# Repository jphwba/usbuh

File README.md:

# Usbuh

This is a USB Hub that features USB-C input, an Auxilary Port with Audio in and out, three USB-A 2.0 ports, two USB-C 2.0 ports and a micro SD Card slot. The main USB hub controllers are two FE1.1s's, a GL823K for the micro-sd controller, an AMS1117-3.3 to step down 5v connections into 3v3 and a PCM2902E for the audio controller. I made this because on my desk the area where my PC is requires the top IO to be blocked which had all of these ports and there was no space to run a cable it was a very tight gap so my current solution is running a $5 temu adapter which goes through a USB-C to USB-A adapter ($0.30 from temu) and a USB1.0 extension cable, so my devices do run pretty slow. So I decided to make this. SInce I'm not very experienced with KiCad and with PCB's and everything, I found USB3.0 a bit more complex and I realised that my design was USB2.0 only too far into the project so I just stuck with 2.0. I also decided later in the project that I wanted an aux port since my headset has an audio/mic combo port and my PC only has split and the adapter I used doesn't work. 

## Printing Notice
Please print 5 connector brakets as there is only 1 in the step file.

## Assembly

The USB Hub has a pretty simple assembly requiring only 4 screws. First in the base plate 4 heatset inserts (M2x3.2mm) go into the standoffs. Then the pcb just goes on top and is screwed in. After this, the walls are placed just on top of the base plate and is attatched with connector brackets I made which go along the sides. Then the top plate just props ontop of the walls and then the front cover is attatched by just pressing it into the front of the assembly. 

## Images

### PCB

### PCB Render

### Schematic

### PCB Order

## Bill of Materials: PLEASE NOTE ALL PRICES ARE IN AUSTRALIAN DOLLARS
|Reference                |Qty|Value                      |Footprint                                                            |Datasheet                                                                        |Item Name                                                                                                                       |Qty|Variation                                  |Price (AUD)|Shipping Fee (If Applicable)|Reference                                                                                                                                                                                                                                                                                                                                                                                                                                                                                                                                                                                                                                                                                                                                                                      |
|Reference                |Qty|Value                      |Footprint                                                            |Datasheet                                                                        |Item Name              |Qty|Variation                                                                                      |Price (USD)|Shipping Fee (If Applicable)|Reference                                                         |
|-------------------------|---|---------------------------|---------------------------------------------------------------------|---------------------------------------------------------------------------------|-----------------------|---|-----------------------------------------------------------------------------------------------|-----------|----------------------------|------------------------------------------------------------------|
|AUX_1                    |1  |AudioJack4                 |Connector_Audio:Jack_3.5mm_PJ320D_Horizontal                         |                                                                                 |PJ-320D                |10 |3.5mm Headphone Jack 0.5A 30V Surface Mount                                                    | $0.51     |                            |https://www.lcsc.com/product-detail/C431535.html                  |
|C1,C2,C8,C9,C13          |5  |10uF                       |Capacitor_SMD:C_0805_2012Metric                                      |                                                                                 |CS2012X7R106M100NRE    |10 |10uF �20% 10V Ceramic Capacitor X7R 0805                                                       | $0.81     |                            |https://www.lcsc.com/product-detail/C5189822.html                 |
|C3,C6,C7,C10,C15         |5  |100nF                      |Capacitor_SMD:C_0805_2012Metric                                      |                                                                                 |CL21B104KBCNNNC        |20 |100nF �10% 50V Ceramic Capacitor X7R 0805                                                      | $0.30     |                            |https://www.lcsc.com/product-detail/C1711.html                    |
|C4,C5,C11,C12,C22,C23    |6  |22pF                       |Capacitor_SMD:C_0805_2012Metric                                      |                                                                                 |CL21C220JBANNNC        |50 |22pF �5% 50V Ceramic Capacitor C0G 0805                                                        | $0.62     |                            |https://www.lcsc.com/product-detail/C1804.html                    |
|C14                      |1  |22uF                       |Capacitor_SMD:C_1206_3216Metric                                      |                                                                                 |CL21A226MOQNNNE        |10 |22uF �20% 16V Ceramic Capacitor X5R 0805                                                       | $1.06     |                            |https://www.lcsc.com/product-detail/C98190.html                   |
|C16,C17,C19,C20,C21,C26  |6  |1uF                        |Capacitor_SMD:C_0805_2012Metric                                      |                                                                                 |CL21B105KAFNNNE        |10 |1uF �10% 25V Ceramic Capacitor X7R 0805                                                        | $0.41     |                            |https://www.lcsc.com/product-detail/C116352.html                  |
|C18                      |1  |2.2uF                      |Capacitor_SMD:C_0805_2012Metric                                      |                                                                                 |CL21A225KBQNNNE        |10 |2.2uF �10% 50V Ceramic Capacitor X5R 0805                                                      | $0.54     |                            |https://www.lcsc.com/product-detail/C377773.html                  |
|C24,C25                  |2  |100uF                      |Capacitor_SMD:C_1210_3225Metric                                      |                                                                                 |CL21A107MQYNNWE        |4  |100uF �20% 6.3V Ceramic Capacitor X5R 0805                                                     | $2.95     |                            |https://www.lcsc.com/product-detail/C6882730.html                 |
|F1,F2,F5,F6,F7           |5  |1A                         |Fuse:Fuse_1206_3216Metric                                            |                                                                                 |BSMD1206-100-30V       |10 |Polymeric PTC Resettable Fuse 30V 1A Surface Mount 1206                                        | $1.01     |                            |https://www.lcsc.com/product-detail/C5358568.html                 |
|Input1,USB_C_1,USB_C_2   |3  |USB_C_Receptacle_USB2.0_16P|Connector_USB:USB_C_Receptacle_GCT_USB4105-xx-A_16P_TopMnt_Horizontal|https://www.usb.org/sites/default/files/documents/usb_type-c.zip                 |USB4105-GF-A-060       |3  |USB 2.0 1 12P -40?~+85? Surface Mount, Right Angle SMD USB, DVI, HDMI Connector Assemblies RoHS| $4.42     |                            |https://www.lcsc.com/product-detail/C3025063.html                 |
|MICRO_SD1                |1  |Micro_SD_Card              |Connector_Card:microSD_HC_Hirose_DM3AT-SF-PEJM5                      |https://www.we-online.com/components/products/datasheet/693072010801.pdf         |DM3AT-SF-PEJM5         |1  |Micro SD card (TF card) Connector and Ejector Push-Push Surface Mount                          | $1.40     |                            |https://www.lcsc.com/product-detail/C114218.html                  |
|R1,R2                    |2  |5.1k                       |Resistor_SMD:R_0805_2012Metric                                       |                                                                                 |0805W8F5101T5E         |100|5.1k? �1% 125mW 0805 Thick Film Resistor                                                       | $0.53     |                            |https://www.lcsc.com/product-detail/C27834.html                   |
|R3,R11                   |2  |2.7k                       |Resistor_SMD:R_0805_2012Metric                                       |                                                                                 |FRC0805J272 TS         |100|2.7k? �5% 125mW 0805 Thick Film Resistor                                                       | $0.32     |                            |https://www.lcsc.com/product-detail/C2907305.html                 |
|R4,R5,R6,R7,R8,R9,R10,R12|8  |10k                        |Resistor_SMD:R_0805_2012Metric                                       |                                                                                 |FRC0805F1002TS         |100|10k? �1% 125mW 0805 Thick Film Resistor                                                        | $0.34     |                            |https://www.lcsc.com/product-detail/C2907219.html                 |
|R13,R14,R15,R16          |4  |56k                        |Resistor_SMD:R_0805_2012Metric                                       |                                                                                 |0805W8F5602T5E         |100|56k? �1% 125mW 0805 Thick Film Resistor                                                        | $0.30     |                            |https://www.lcsc.com/product-detail/C17756.html                   |
|R17,R18                  |2  |22                         |Resistor_SMD:R_0805_2012Metric                                       |                                                                                 |FRC0805J220 TS         |100|22? �5% 125mW 0805 Thick Film Resistor                                                         | $0.33     |                            |https://www.lcsc.com/product-detail/C2907310.html                 |
|R19                      |1  |2.2k                       |Resistor_SMD:R_0805_2012Metric                                       |                                                                                 |0805W8F2201T5E         |100|2.2k? �1% 125mW 0805 Thick Film Resistor                                                       | $0.44     |                            |https://www.lcsc.com/product-detail/C17520.html                   |
|U1,U2                    |2  |FE1.1s                     |Package_SO:SSOP-28_3.9x9.9mm_P0.635mm                                |https://cdn-shop.adafruit.com/product-files/2991/FE1.1s+Data+Sheet+(Rev.+1.0).pdf|FE1.1S-BSOP28BCN       |2  |4 USB Hub 480Mbps USB 2.0 SSOP-28-150mil Interface Controllers RoHS                            | $1.39     |                            |https://www.lcsc.com/product-detail/C9359.html                    |
|U3                       |1  |GL823K                     |GL823K:SOP64P600X175-16N                                             |                                                                                 |GL823K-HCY04           |1  |USB to SD 480Mbps USB 2.0 SSOP-16-150mil Interface Controllers RoHS                            | $0.46     |                            |https://www.lcsc.com/product-detail/C284879.html                  |
|U4                       |1  |AMS1117-3.3                |Package_TO_SOT_SMD:SOT-223-3_TabPin2                                 |http://www.advanced-monolithic.com/pdf/ds1117.pdf                                |AMS1117-3.3            |5  |3.3V Positive Fixed SOT-223 Voltage Regulators - Linear, Low Drop Out (LDO) Regulators RoHS    | $1.05     |                            |https://www.lcsc.com/product-detail/C6186.html                    |
|U5                       |1  |PCM2902                    |Package_SO:SSOP-28_5.3x10.2mm_P0.65mm                                |http://www.ti.com/lit/ds/symlink/pcm2902c.pdf                                    |PCM2902CDBR            |1  |Encoder/decoder USB 8kHz~48kHz SSOP-28 CODECS RoHS                                             | $12.21    |                            |https://www.lcsc.com/product-detail/C2651869.html                 |
|USB_A_1                  |1  |USB_A                      |Connector_USB:USB_A_Receptacle_GCT_USB1046                           |                                                                                 |USB1046-GF-0190-L-B-A  |1  |USB 2.0 1 4P -40?~+85? SMD USB, DVI, HDMI Connector Assemblies RoHS                            | $1.35     |                            |https://www.lcsc.com/product-detail/C6307429.html                 |
|USB_A_STACKED_2&3        |1  |USB_A_Stacked              |Connector_USB:USB_A_Wuerth_61400826021_Horizontal_Stacked            |                                                                                 |907-111A1012D10200     |5  |USB-A (USB TYPE-A) Receptacle Connector 8 Position Through Hole                                | $0.93     |                            |https://www.lcsc.com/product-detail/C2341.html                    |
|Y1,Y2,Y3                 |3  |12MHz                      |Crystal:Crystal_SMD_3225-4Pin_3.2x2.5mm                              |                                                                                 |X322512MSB4SI          |5  |Crystal 12MHz �10ppm 20pF SMD3225-4P                                                           | $0.48     |                            |https://www.lcsc.com/product-detail/C9002.html                    |
|Heatset Inserts          |4  |M2x3.2mm                   |                                                                     |                                                                                 |M2x3.2mm heatset insert|4  |Brass Threaded Heat-Set Insert [M2x3x3.2]                                                      | $2.16     | $10.00                     |https://www.3dprintergear.com.au/m2-brass-threaded-heat-set-insert|
|PCB                      |1  |90x55                      |                                                                     |                                                                                 |JLPCB                  |   |                                                                                               | $23.00    |                            |                                                                  |
|Printing Legion          |1  |                           |                                                                     |                                                                                 |                       |   |                                                                                               | $14.00    |                            |                                                                  |
|LCSC Shipping            |   |                           |                                                                     |                                                                                 |LCSC Shipping - 4PX    |   |                                                                                               | $14.97    |                            |                                                                  |
|                         |   |                           |Total Price:                                                         |                                                                                 |                       |   |                                                                                               | $98.29    |                            |                                                                  |
|                         |   |                           |                                                                     |                                                                                 |                       |   |                                                                                               |           |                            |                                                                  |
|                         |   |                           |                                                                     |                                                                                 |                       |   |                                                                                               |           |                            |                                                                  |
|                         |   |                           |                                                                     |                                                                                 |                       |   |                                                                                               |           |                            |                                                                  |

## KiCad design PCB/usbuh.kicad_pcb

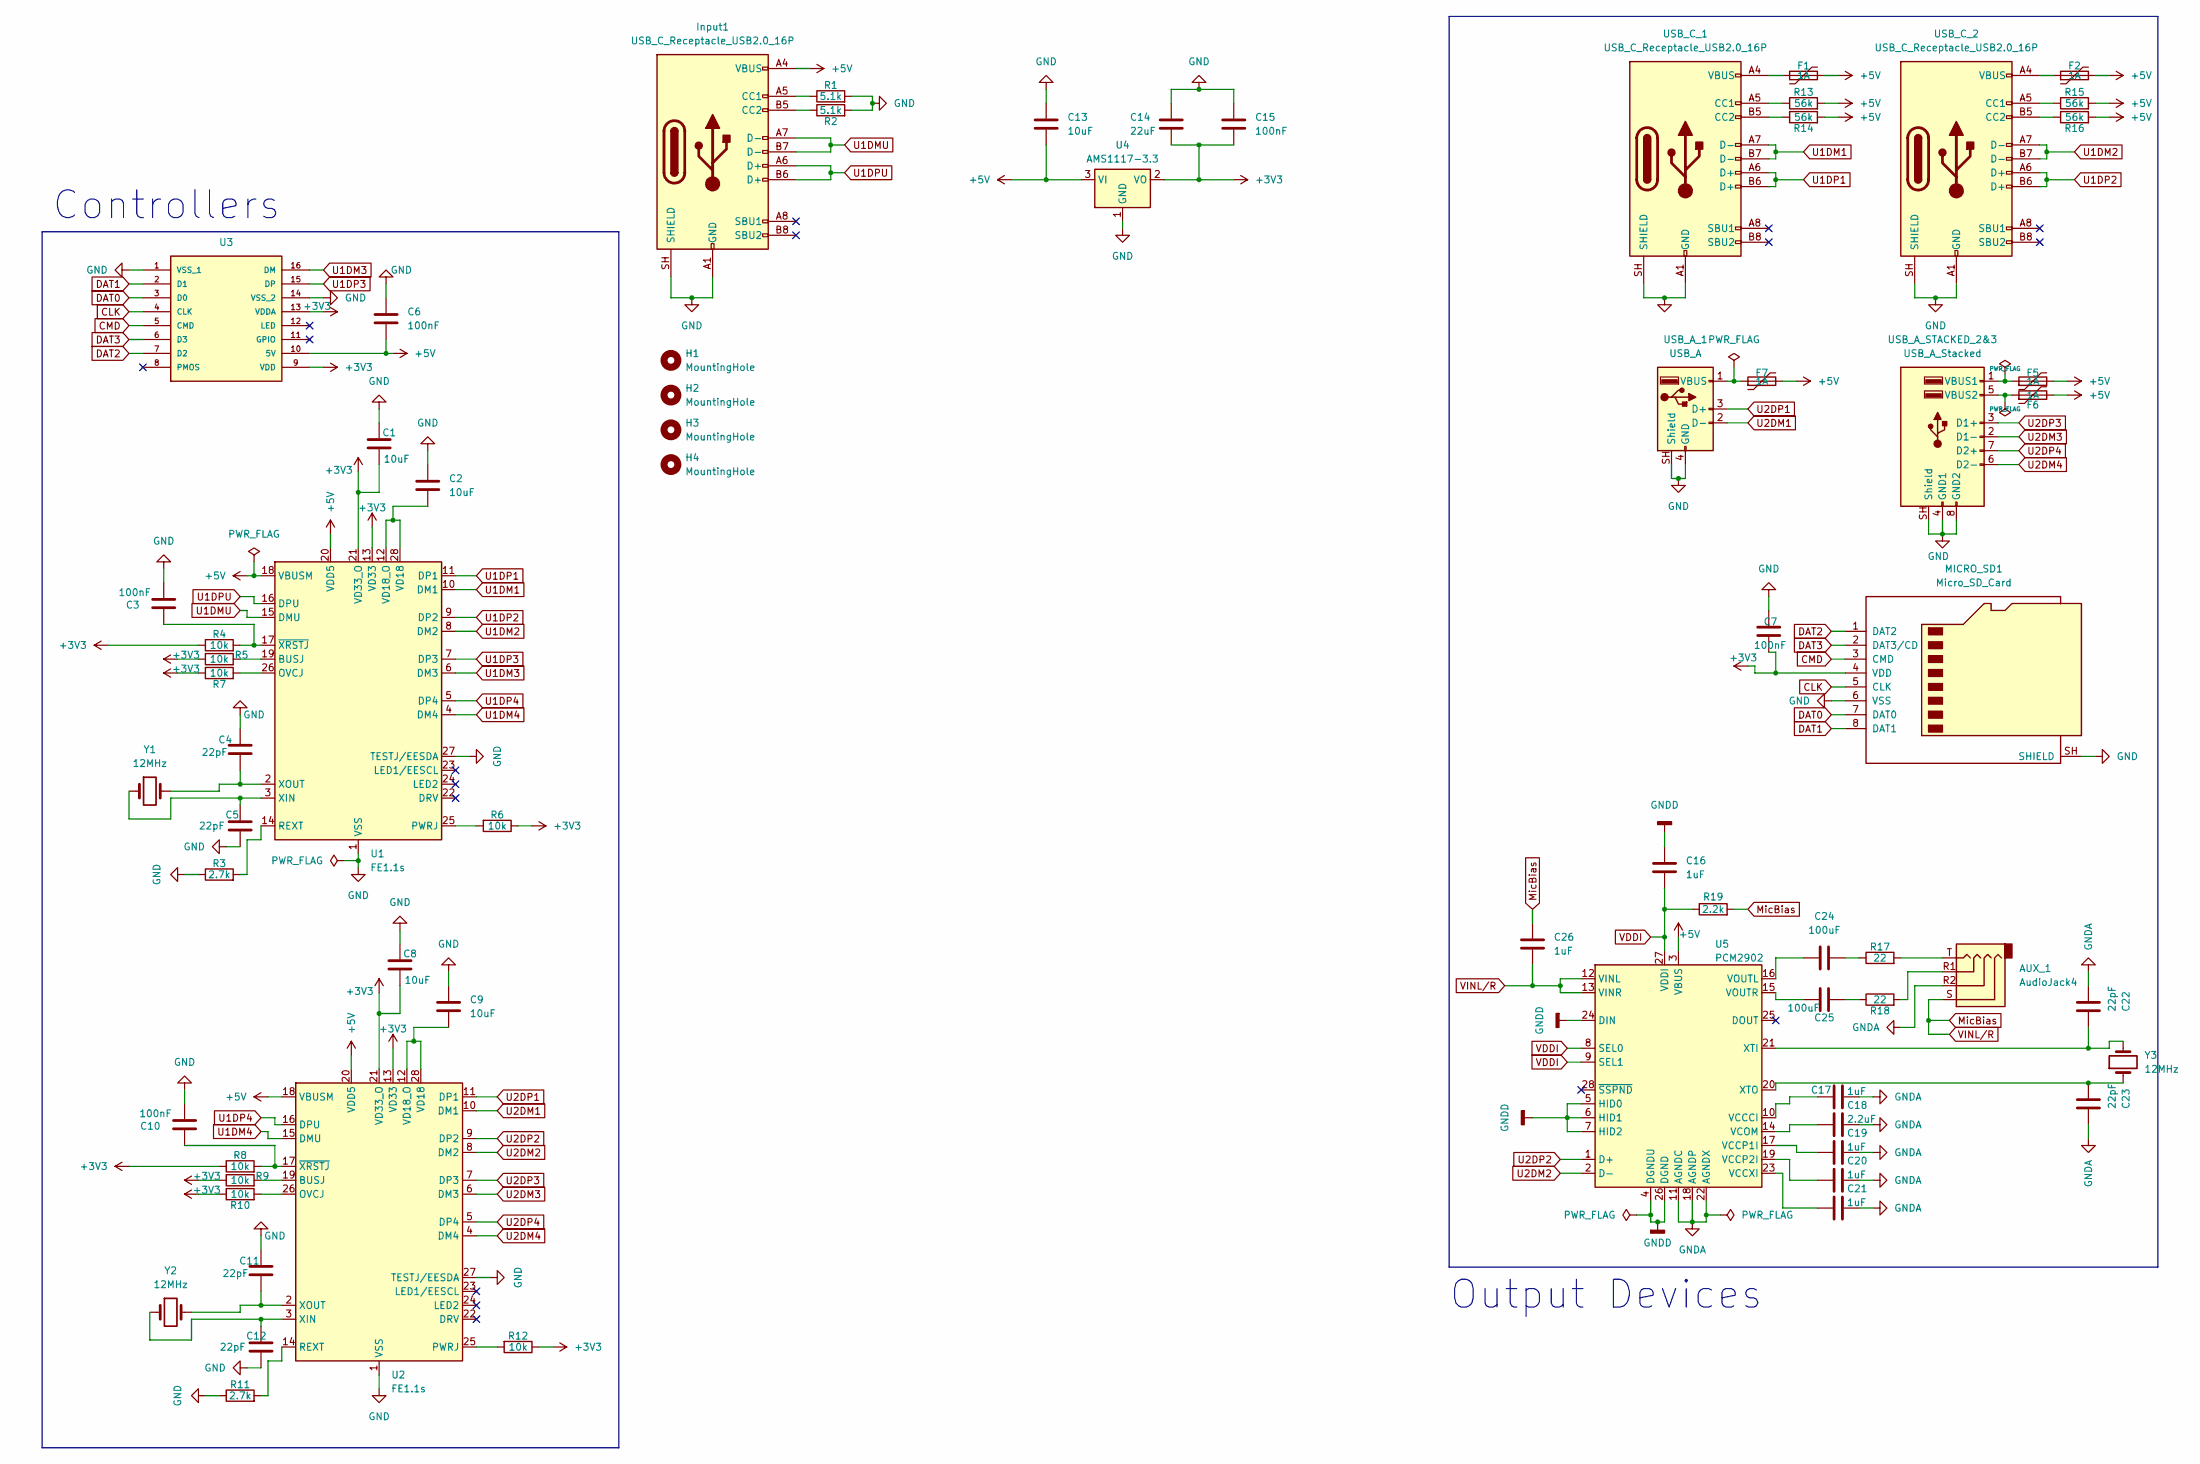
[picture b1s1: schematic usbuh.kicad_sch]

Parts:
AUX_1: AudioJack4; Jack_3.5mm_PJ320D_Horizontal
C1, C2, C8, C9, C13: 10uF; C_0805_2012Metric
C3, C6, C7, C10, C15: 100nF; C_0805_2012Metric
C4, C5, C11, C12, C22, C23: 22pF; C_0805_2012Metric
C14: 22uF; C_1206_3216Metric
C16, C17, C19, C20, C21, C26: 1uF; C_0805_2012Metric
C18: 2.2uF; C_0805_2012Metric
C24, C25: 100uF; C_1210_3225Metric
F1, F2, F5, F6, F7: 1A; Fuse_1206_3216Metric
H1, H2, H3, H4: MountingHole; MountingHole_2.1mm
Input1: USB_C_Receptacle_USB2.0_16P; USB_C_Receptacle_GCT_USB4105-xx-A_16P_TopMnt_Horizontal
MICRO_SD1: Micro_SD_Card; microSD_HC_Hirose_DM3AT-SF-PEJM5
R1, R2: 5.1k; R_0805_2012Metric
R3, R11: 2.7k; R_0805_2012Metric
R4, R5, R6, R7, R8, R9, R10, R12: 10k; R_0805_2012Metric
R13, R14, R15, R16: 56k; R_0805_2012Metric
R17, R18: 22; R_0805_2012Metric
R19: 2.2k; R_0805_2012Metric
U1, U2: FE1.1s; SSOP-28_3.9x9.9mm_P0.635mm
U3: SOP64P600X175-16N; MANUFACTURER_PART_NUMBER GL823K
U4: AMS1117-3.3; SOT-223-3_TabPin2
U5: PCM2902; SSOP-28_5.3x10.2mm_P0.65mm
USB_A_1: USB_A; USB_A_Receptacle_GCT_USB1046
USB_A_STACKED_2&3: USB_A_Stacked; USB_A_Wuerth_61400826021_Horizontal_Stacked
USB_C_1, USB_C_2: USB_C_Receptacle_USB2.0_16P; USB_C_Receptacle_GCT_USB4105-xx-A_16P_TopMnt_Horizontal
Y1, Y2, Y3: 12MHz; Crystal_SMD_3225-4Pin_3.2x2.5mm

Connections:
+3V3: C1.1, C7.2, C8.1, C14.2, C15.2, MICRO_SD1.4 (VDD), R4.1, R5.1, R6.1, R7.1, R8.1, R9.1, R10.1, R12.1, U1.13 (VD33), U1.21 (VD33_O), U2.13 (VD33), U2.21 (VD33_O), U3.9 (VDD), U3.13 (VDDA), U4.2 (VO)
+5V: C6.2, C13.2, F1.2, F2.2, F5.2, F6.2, F7.2, Input1.A4 (VBUS), Input1.A9 (VBUS), Input1.B4 (VBUS), Input1.B9 (VBUS), R13.2, R14.2, R15.2, R16.2, U1.18 (VBUSM), U1.20 (VDD5), U2.18 (VBUSM), U2.20 (VDD5), U3.10 (5V), U4.3 (VI), U5.3 (VBUS)
CLK: MICRO_SD1.5 (CLK), U3.4 (CLK)
CMD: MICRO_SD1.3 (CMD), U3.5 (CMD)
DAT0: MICRO_SD1.7 (DAT0), U3.3 (D0)
DAT1: MICRO_SD1.8 (DAT1), U3.2 (D1)
DAT2: MICRO_SD1.1 (DAT2), U3.7 (D2)
DAT3: MICRO_SD1.2 (DAT3/CD), U3.6 (D3)
GND: C1.2, C2.2, C3.2, C4.1, C5.2, C6.1, C7.1, C8.2, C9.2, C10.2, C11.1, C12.2, C13.1, C14.1, C15.1, Input1.A1 (GND), Input1.A12 (GND), Input1.B1 (GND), Input1.B12 (GND), Input1.SH (SHIELD), MICRO_SD1.6 (VSS), MICRO_SD1.SH (SHIELD), R1.2, R2.2, R3.1, R11.1, U1.1 (VSS), U1.27 (TESTJ/EESDA), U2.1 (VSS), U2.27 (TESTJ/EESDA), U3.1 (VSS_1), U3.14 (VSS_2), U4.1 (GND), USB_A_1.4 (GND), USB_A_1.SH (Shield), USB_A_STACKED_2&3.4 (GND1), USB_A_STACKED_2&3.8 (GND2), USB_A_STACKED_2&3.SH (Shield), USB_C_1.A1 (GND), USB_C_1.A12 (GND), USB_C_1.B1 (GND), USB_C_1.B12 (GND), USB_C_1.SH (SHIELD), USB_C_2.A1 (GND), USB_C_2.A12 (GND), USB_C_2.B1 (GND), USB_C_2.B12 (GND), USB_C_2.SH (SHIELD)
GNDA: AUX_1.R2, C17.2, C18.2, C19.2, C20.2, C21.2, C22.2, C23.1, U5.11 (AGNDC), U5.18 (AGNDP), U5.22 (AGNDX)
GNDD: C16.2, U5.4 (DGNDU), U5.5 (HID0), U5.6 (HID1), U5.7 (HID2), U5.24 (DIN), U5.26 (DGND)
MicBias: AUX_1.S, C26.1, C26.2, R19.2, U5.12 (VINL), U5.13 (VINR)
unnamed: AUX_1.R1, R18.2
unnamed: AUX_1.T, R17.2
unnamed: C24.2, R17.1
unnamed: C25.2, R18.1
unnamed: F1.1, USB_C_1.A4 (VBUS), USB_C_1.A9 (VBUS), USB_C_1.B4 (VBUS), USB_C_1.B9 (VBUS)
unnamed: F2.1, USB_C_2.A4 (VBUS), USB_C_2.A9 (VBUS), USB_C_2.B4 (VBUS), USB_C_2.B9 (VBUS)
unnamed: Input1.A5 (CC1), R1.1
unnamed: Input1.B5 (CC2), R2.1
unnamed: R5.2, U1.19 (BUSJ)
unnamed: R7.2, U1.26 (OVCJ)
unnamed: R6.2, U1.25 (PWRJ)
unnamed: R3.2, U1.14 (REXT)
unnamed: C2.1, U1.12 (VD18_O), U1.28 (VD18)
unnamed: C5.1, U1.3 (XIN), Y1.1
unnamed: C4.2, U1.2 (XOUT), Y1.2
unnamed: C3.1, R4.2, U1.17 (~XRSTJ)
unnamed: R9.2, U2.19 (BUSJ)
unnamed: R10.2, U2.26 (OVCJ)
unnamed: R12.2, U2.25 (PWRJ)
unnamed: R11.2, U2.14 (REXT)
unnamed: C9.1, U2.12 (VD18_O), U2.28 (VD18)
unnamed: C12.1, U2.3 (XIN), Y2.1
unnamed: C11.2, U2.2 (XOUT), Y2.2
unnamed: C10.1, R8.2, U2.17 (~XRSTJ)
unnamed: C17.1, U5.10 (VCCCI)
unnamed: C19.1, U5.17 (VCCP1I)
unnamed: C20.1, U5.19 (VCCP2I)
unnamed: C21.1, U5.23 (VCCXI)
unnamed: C18.1, U5.14 (VCOM)
unnamed: C24.1, U5.16 (VOUTL)
unnamed: C25.1, U5.15 (VOUTR)
unnamed: C22.1, U5.21 (XTI), Y3.2
unnamed: C23.2, U5.20 (XTO), Y3.1
unnamed: F7.1, USB_A_1.1 (VBUS)
unnamed: F5.1, USB_A_STACKED_2&3.1 (VBUS1)
unnamed: F6.1, USB_A_STACKED_2&3.5 (VBUS2)
unnamed: R13.1, USB_C_1.A5 (CC1)
unnamed: R14.1, USB_C_1.B5 (CC2)
unnamed: R15.1, USB_C_2.A5 (CC1)
unnamed: R16.1, USB_C_2.B5 (CC2)
U1DM1: U1.10 (DM1), USB_C_1.A7 (D-), USB_C_1.B7 (D-)
U1DM2: U1.8 (DM2), USB_C_2.A7 (D-), USB_C_2.B7 (D-)
U1DM3: U1.6 (DM3), U3.16 (DM)
U1DM4: U1.4 (DM4), U2.15 (DMU)
U1DMU: Input1.A7 (D-), Input1.B7 (D-), U1.15 (DMU)
U1DP1: U1.11 (DP1), USB_C_1.A6 (D+), USB_C_1.B6 (D+)
U1DP2: U1.9 (DP2), USB_C_2.A6 (D+), USB_C_2.B6 (D+)
U1DP3: U1.7 (DP3), U3.15 (DP)
U1DP4: U1.5 (DP4), U2.16 (DPU)
U1DPU: Input1.A6 (D+), Input1.B6 (D+), U1.16 (DPU)
U2DM1: U2.10 (DM1), USB_A_1.2 (D-)
U2DM2: U2.8 (DM2), U5.2 (D-)
U2DM3: U2.6 (DM3), USB_A_STACKED_2&3.2 (D1-)
U2DM4: U2.4 (DM4), USB_A_STACKED_2&3.6 (D2-)
U2DP1: U2.11 (DP1), USB_A_1.3 (D+)
U2DP2: U2.9 (DP2), U5.1 (D+)
U2DP3: U2.7 (DP3), USB_A_STACKED_2&3.3 (D1+)
U2DP4: U2.5 (DP4), USB_A_STACKED_2&3.7 (D2+)
VDDI: C16.1, R19.1, U5.8 (SEL0), U5.9 (SEL1), U5.27 (VDDI)

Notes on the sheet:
Output Devices
Controllers

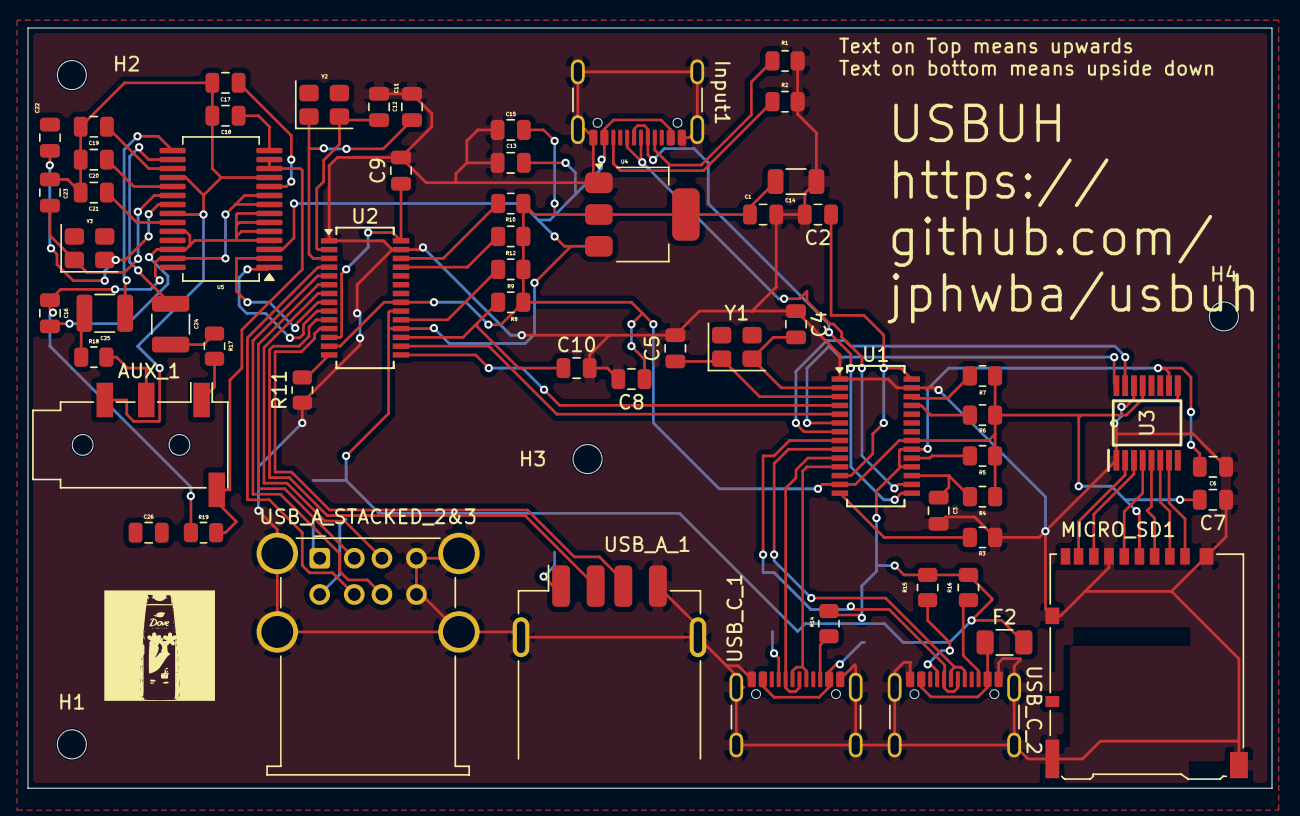
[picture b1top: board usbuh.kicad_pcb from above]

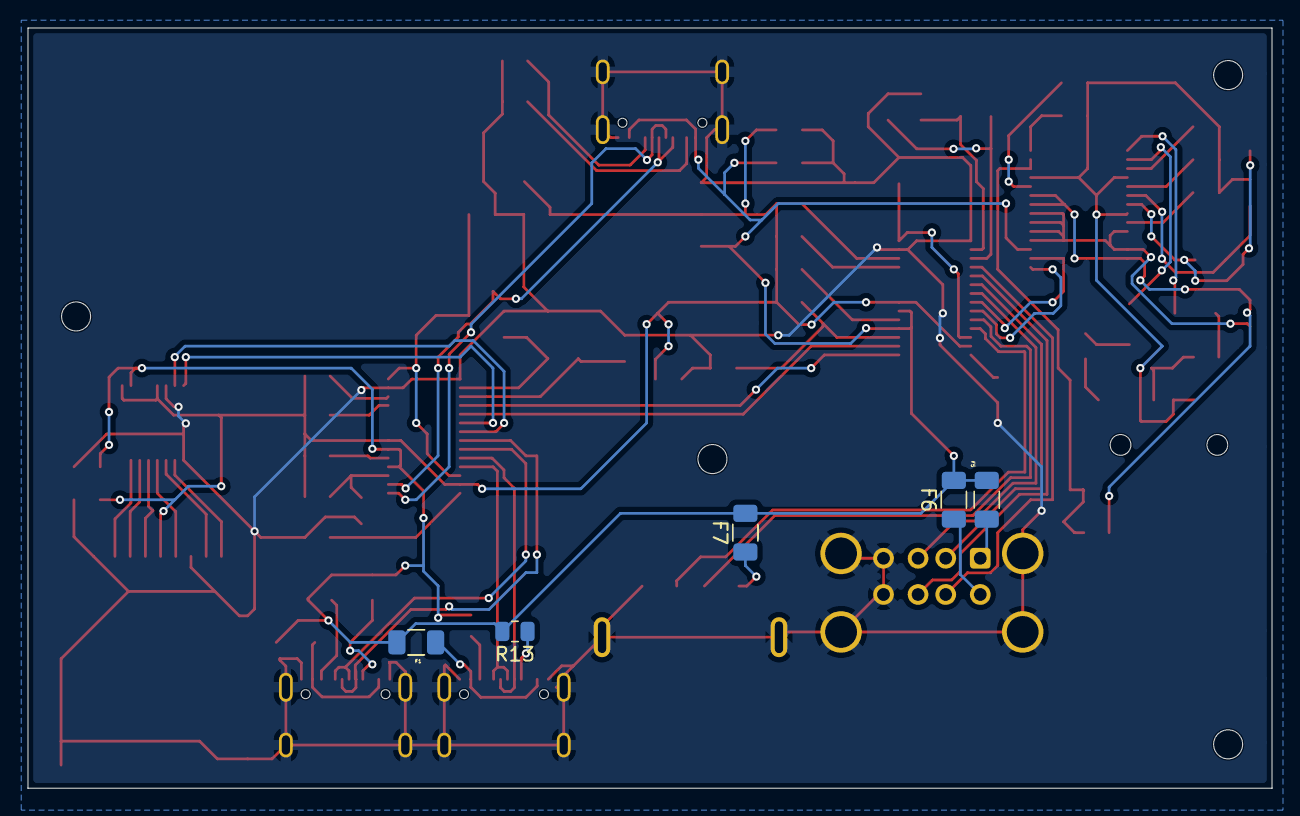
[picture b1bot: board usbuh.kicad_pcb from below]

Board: 2 copper layers, 90.0 x 55.0 mm, 69 parts (5 on the bottom side), 71 nets.

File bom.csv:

Reference,Qty,Value,Footprint,Datasheet,Item Name,Qty,Variation, Price (AUD) , Shipping Fee (If Applicable) ,Reference
AUX_1,1,AudioJack4,Connector_Audio:Jack_3.5mm_PJ320D_Horizontal,,10PCS 3.5MM Headphone Jack PJ-320D Audio Jack 4 Pin SMD SMT MP3 Accessories PJ320D,1,,$1.69,,https://www.aliexpress.com/item/4000661908135.html?spm=a2g0o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
"C1,C2,C8,C9,C13",5,10uF,Capacitor_SMD:C_0805_2012Metric,,20PCS 0805 2012 SMD Capacitor 1UF 2.2UF 4.7UF 10UF 22UF 47UF 100UF 6V3 10V 16V 25V 35V 50V 63V 100V X7R X5R K=±10% M=±20%,1,Capacitance: 0805 10UF 10V X7R K,$1.43,,https://www.aliexpress.com/item/1005007533370902.html?spm=a2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
"C3,C6,C7,C10,C15",5,100nF,Capacitor_SMD:C_0805_2012Metric,,50PCS 0805 100NF 104K 50V 100V 250V 10% X7R 2012 SMD Chip Multilayer Ceramic Capacitor ,1,(Capacitance: 0805 100NF 104K 50V),$1.76,,https://www.aliexpress.com/item/1005007533532838.html?spm=a2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
"C4,C5,C11,C12,C22,C23",6,22pF,Capacitor_SMD:C_0805_2012Metric,,100PCS 0805 C0805 20pF 50V 2012 Capacitor 1PF-47UF ( 10PF 22PF 47PF 100PF 1NF 2.2NF 10NF 100NF 1UF 2.2UF 4.7UF 10UF 22UF ) ,1,(Capacitance: 22PF),$2.15,,https://www.aliexpress.com/item/1106549969.html?spm=a2g0o.pr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
C14,1,22uF,Capacitor_SMD:C_1206_3216Metric,,20PCS 0805 2012 SMD Capacitor 1UF 2.2UF 4.7UF 10UF 22UF 47UF 100UF 6V3 10V 16V 25V 35V 50V 63V 100V X7R X5R K=±10% M=±20% ,1,(Capacitance: 0805 22UF 10V X7R K),$1.50,,https://www.aliexpress.com/item/1005007533370902.html?spm=a2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
"C16,C17,C19,C20,C21,C26",6,1uF,Capacitor_SMD:C_0805_2012Metric,,100PCS 0805 C0805 20pF 50V 2012 Capacitor 1PF-47UF ( 10PF 22PF 47PF 100PF 1NF 2.2NF 10NF 100NF 1UF 2.2UF 4.7UF 10UF 22UF ) ,1,(Capacitance: 1UF),$2.15,,https://www.aliexpress.com/item/1106549969.html?spm=a2g0o.pr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
C18,1,2.2uF,Capacitor_SMD:C_0805_2012Metric,,100PCS 0805 C0805 20pF 50V 2012 Capacitor 1PF-47UF ( 10PF 22PF 47PF 100PF 1NF 2.2NF 10NF 100NF 1UF 2.2UF 4.7UF 10UF 22UF ) ,1,(Capacitance: 2.2UF),$2.15,,https://www.aliexpress.com/item/1106549969.html?spm=a2g0o.pr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
"C24,C25",2,100uF,Capacitor_SMD:C_1210_3225Metric,,20PCS 0805 SMD Capacitor 1UF 2.2UF 4.7UF 10UF 22UF 47UF 100UF 6V3 10V 16V 25V 35V 50V 63V 100V X7R X5R K=±10% M=±20%,1,Resistance: 0805 100UF 10V X5R M,$13.29,,https://www.aliexpress.com/item/1005006815492689.html?spm=a2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
"F1,F2,F5,F6,F7",5,1A,Fuse:Fuse_1206_3216Metric,,3216 1206 0.05A 0.1A 0.12A 0.16A 0.2A 0.25A 0.5A 0.75A 1.1A 2A SMD Resettable Fuse PPTC PolySwitch Self-Recovery Fuse,1,"(AMP: 1A, Size: 1206, Temperature: 20 Pcs)",$3.38,,https://www.aliexpress.com/item/1005004273302126.html?spm=a2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
"Input1,USB_C_1,USB_C_2",3,USB_C_Receptacle_USB2.0_16P,Connector_USB:USB_C_Receptacle_GCT_USB4105-xx-A_16P_TopMnt_Horizontal,https://www.usb.org/sites/default/files/documents/usb_type-c.zip,10-100Pcs USB4105-GF-A 16Pin Type-C Female Socket SMT Top Mount PCB Receptacle USB2.0 16P Right Angle SMD Connector Replacement ,1,(Color: 10pcs),$4.89,,https://www.aliexpress.com/item/1005012606240318.html?spm=a2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
MICRO_SD1,1,Micro_SD_Card,Connector_Card:microSD_HC_Hirose_DM3AT-SF-PEJM5,https://www.we-online.com/components/products/datasheet/6930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,100% brand new original connector DM3AT-SF-PEJM5 micro SD memory card slot TF card slot 10P ,1,(Model Number: 1pcs),$0.77,$9.48,https://www.aliexpress.com/item/1005009087733553.html?spm=a2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
"R1,R2",2,5.1k,Resistor_SMD:R_0805_2012Metric,,100PCS 0805 5% 0R-10M 1R 2.2R 10R 22R 47R 100R 560R 1K2 6.8K 10K 12K 20K 47K 100K 510K 910K 1M 4.7M 9.1M 1/8W ,1,(Resistance: 5.1k),$0.55,$2.85,https://www.aliexpress.com/item/1005004542018347.html?spm=a2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
"R3,R11",2,2.7k,Resistor_SMD:R_0805_2012Metric,,100PCS 0805 5% 0R-10M 1R 2.2R 10R 22R 47R 100R 560R 1K2 6.8K 10K 12K 20K 47K 100K 510K 910K 1M 4.7M 9.1M 1/8W ,1,(Resistance: 2.7k),$0.55,$2.85,https://www.aliexpress.com/item/1005004542018347.html?spm=a2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
"R4,R5,R6,R7,R8,R9,R10,R12",8,10k,Resistor_SMD:R_0805_2012Metric,,100PCS 0805 5% 0R-10M 1R 2.2R 10R 22R 47R 100R 560R 1K2 6.8K 10K 12K 20K 47K 100K 510K 910K 1M 4.7M 9.1M 1/8W ,1,(Resistance: 10k),$0.55,$2.85,https://www.aliexpress.com/item/1005004542018347.html?spm=a2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
"R13,R14,R15,R16",4,56k,Resistor_SMD:R_0805_2012Metric,,100PCS 0805 5% 0R-10M 1R 2.2R 10R 22R 47R 100R 560R 1K2 6.8K 10K 12K 20K 47K 100K 510K 910K 1M 4.7M 9.1M 1/8W ,1,(Resistance: 56k),$0.55,$2.85,https://www.aliexpress.com/item/1005004542018347.html?spm=a2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
"R17,R18",2,22,Resistor_SMD:R_0805_2012Metric,,100PCS 0805 5% 0R-10M 1R 2.2R 10R 22R 47R 100R 560R 1K2 6.8K 10K 12K 20K 47K 100K 510K 910K 1M 4.7M 9.1M 1/8W ,1,(Resistance: 22R),$0.55,$2.85,https://www.aliexpress.com/item/1005004542018347.html?spm=a2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
R19,1,2.2k,Resistor_SMD:R_0805_2012Metric,,100PCS 0805 5% 0R-10M 1R 2.2R 10R 22R 47R 100R 560R 1K2 6.8K 10K 12K 20K 47K 100K 510K 910K 1M 4.7M 9.1M 1/8W ,1,(Resistance: 2.2k),$0.55,$2.85,https://www.aliexpress.com/item/1005004542018347.html?spm=a2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
"U1,U2",2,FE1.1s,Package_SO:SSOP-28_3.9x9.9mm_P0.635mm,https://cdn-shop.adafruit.com/product-files/2991/FE1.1s+Data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,10Pcs 100% New original USB chip FE1.1s USB2.0 HUB shunt SSOP-28 IC Chip in stock,1,,$5.39,,https://www.aliexpress.com/item/1005004507102883.html?spm=a2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
U3,1,GL823K,GL823K:SOP64P600X175-16N,,5PCS MAX5456EEE MAX5456 MAX3221CDBR MA3221C MA3221 ZXCD1000EQ16TA ZXCD1000 GL823K GL823 FT230XS FT230 SSOP-16 ,1,(Color: GL823K),$7.79,$5.15,https://www.aliexpress.com/item/1005012942277018.html?spm=a2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
U4,1,AMS1117-3.3,Package_TO_SOT_SMD:SOT-223-3_TabPin2,http://www.advanced-monolithic.com/pdf/ds1117.pdf,50PCS AMS1117 3V3 AMS1117-3.3 SOT223 Voltage Rugulator,1,Color: AMS1117-3.3(50PCS),$7.88,,https://www.aliexpress.com/item/1005007416774959.html?spm=a2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
U5,1,PCM2902,Package_SO:SSOP-28_5.3x10.2mm_P0.65mm,http://www.ti.com/lit/ds/symlink/pcm2902c.pdf,100%New Original PCM2902E PCM2902 SSOP-28 In Stock,1,(Color: 2PCS),$3.24,,https://www.aliexpress.com/item/1005005459552093.html?spm=a2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
"Y1,Y2,Y3",3,12MHz,Crystal:Crystal_SMD_3225-4Pin_3.2x2.5mm,,10PCS SMD 3225 SMD passive quartz crystal oscillator 8Mhz 10Mhz 12Mhz 16Mhz 20Mhz 24Mhz 26Mhz 30Mhz 32Mhz 40Mhz 48Mhz 8.000Mhz ,1,(Color: 12Mhz),$2.81,$2.93,https://www.aliexpress.com/item/1005004389041900.html?spm=a2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
Heatset Inserts,4,M2x3.2mm,,,10/15/20/40/50/100pcs M1 M1.2 M1.4 M2 M2.5 M3 M4 M5 M6 M8 Thread Knurled Brass Heat Insert Nut Copper Embedment Embed Parts Nuts,1,"Size: M2x3.2mm (50pcs), Color: Length 3.5mm",$3.37,$2.14,https://www.aliexpress.com/item/1005007424930348.html?spm=a2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
Screws,4,M2x5mm,,,50/100/200pcs M1 M1.2 M1.4 M1.6 M2 M2.5 M3 M4 Cross Recessed Phillips Flat Countersunk Head Screw Bolt GB819 Black Carbon Steel,1,Length: 100pcs M2x5mm,$3.91,,https://www.aliexpress.com/item/1005006995421098.html?spm=a2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
PCB,1,90x55,,,JLPCB,,,$23.00,,
Printing Legion,1,,,,,,,$14.00,,
USB_A_1,1,USB_A,Connector_USB:USB_A_Receptacle_GCT_USB1046,,,,,,,
USB_A_STACKED_2&3,1,USB_A_Stacked,Connector_USB:USB_A_Wuerth_61400826021_Horizontal_Stacked,,,,,,,
,,,Total Price:,,,,,$127.65,,
